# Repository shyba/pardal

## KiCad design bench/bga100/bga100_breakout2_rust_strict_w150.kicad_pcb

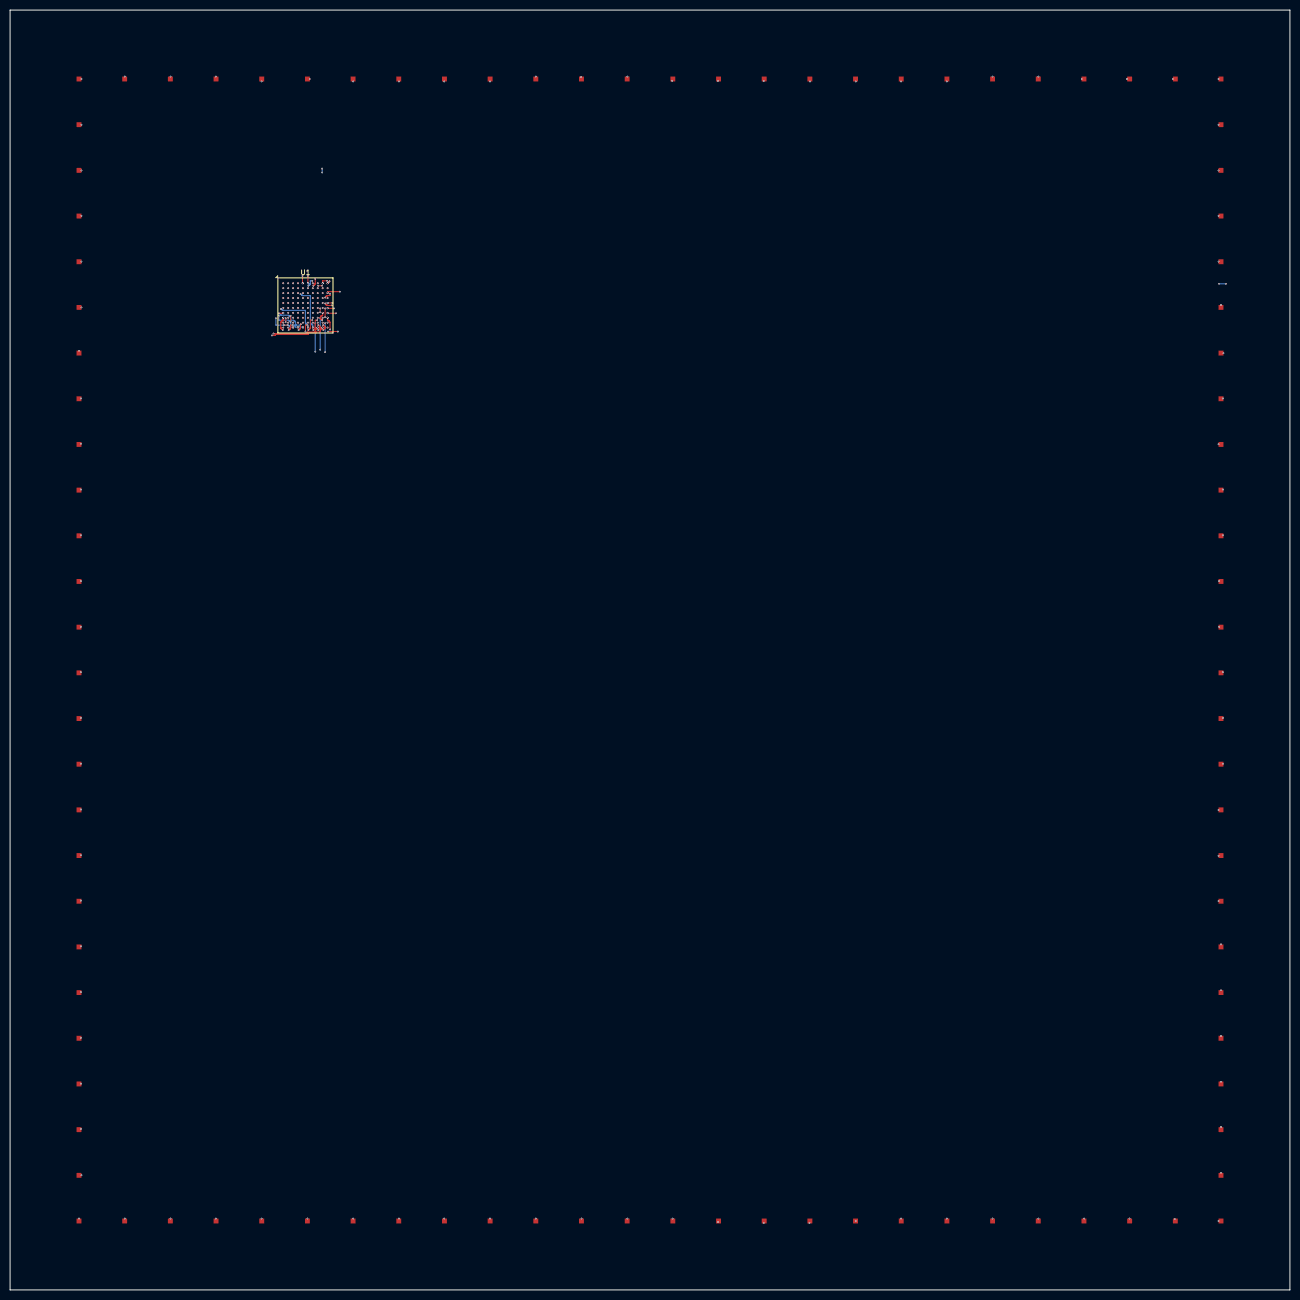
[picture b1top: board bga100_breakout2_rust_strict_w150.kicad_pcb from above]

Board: 4 copper layers, 260.0 x 260.0 mm, 101 parts (0 on the bottom side), 100 nets.

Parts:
TP1: A1; TestPoint_Pad_1.0x1.0mm
TP2: A2; TestPoint_Pad_1.0x1.0mm
TP3: A3; TestPoint_Pad_1.0x1.0mm
TP4: A4; TestPoint_Pad_1.0x1.0mm
TP5: A5; TestPoint_Pad_1.0x1.0mm
TP6: A6; TestPoint_Pad_1.0x1.0mm
TP7: A7; TestPoint_Pad_1.0x1.0mm
TP8: A8; TestPoint_Pad_1.0x1.0mm
TP9: A9; TestPoint_Pad_1.0x1.0mm
TP10: A10; TestPoint_Pad_1.0x1.0mm
TP11: B1; TestPoint_Pad_1.0x1.0mm
TP12: B2; TestPoint_Pad_1.0x1.0mm
TP13: B3; TestPoint_Pad_1.0x1.0mm
TP14: B4; TestPoint_Pad_1.0x1.0mm
TP15: B5; TestPoint_Pad_1.0x1.0mm
TP16: B6; TestPoint_Pad_1.0x1.0mm
TP17: B7; TestPoint_Pad_1.0x1.0mm
TP18: B8; TestPoint_Pad_1.0x1.0mm
TP19: B9; TestPoint_Pad_1.0x1.0mm
TP20: B10; TestPoint_Pad_1.0x1.0mm
TP21: C1; TestPoint_Pad_1.0x1.0mm
TP22: C2; TestPoint_Pad_1.0x1.0mm
TP23: C3; TestPoint_Pad_1.0x1.0mm
TP24: C4; TestPoint_Pad_1.0x1.0mm
TP25: C5; TestPoint_Pad_1.0x1.0mm
TP26: C6; TestPoint_Pad_1.0x1.0mm
TP27: C7; TestPoint_Pad_1.0x1.0mm
TP28: C8; TestPoint_Pad_1.0x1.0mm
TP29: C9; TestPoint_Pad_1.0x1.0mm
TP30: C10; TestPoint_Pad_1.0x1.0mm
TP31: D1; TestPoint_Pad_1.0x1.0mm
TP32: D2; TestPoint_Pad_1.0x1.0mm
TP33: D3; TestPoint_Pad_1.0x1.0mm
TP34: D4; TestPoint_Pad_1.0x1.0mm
TP35: D5; TestPoint_Pad_1.0x1.0mm
TP36: D6; TestPoint_Pad_1.0x1.0mm
TP37: D7; TestPoint_Pad_1.0x1.0mm
TP38: D8; TestPoint_Pad_1.0x1.0mm
TP39: D9; TestPoint_Pad_1.0x1.0mm
TP40: D10; TestPoint_Pad_1.0x1.0mm
TP41: E1; TestPoint_Pad_1.0x1.0mm
TP42: E2; TestPoint_Pad_1.0x1.0mm
TP43: E3; TestPoint_Pad_1.0x1.0mm
TP44: E4; TestPoint_Pad_1.0x1.0mm
TP45: E5; TestPoint_Pad_1.0x1.0mm
TP46: E6; TestPoint_Pad_1.0x1.0mm
TP47: E7; TestPoint_Pad_1.0x1.0mm
TP48: E8; TestPoint_Pad_1.0x1.0mm
TP49: E9; TestPoint_Pad_1.0x1.0mm
TP50: E10; TestPoint_Pad_1.0x1.0mm
TP51: F1; TestPoint_Pad_1.0x1.0mm
TP52: F2; TestPoint_Pad_1.0x1.0mm
TP53: F3; TestPoint_Pad_1.0x1.0mm
TP54: F4; TestPoint_Pad_1.0x1.0mm
TP55: F5; TestPoint_Pad_1.0x1.0mm
TP56: F6; TestPoint_Pad_1.0x1.0mm
TP57: F7; TestPoint_Pad_1.0x1.0mm
TP58: F8; TestPoint_Pad_1.0x1.0mm
TP59: F9; TestPoint_Pad_1.0x1.0mm
TP60: F10; TestPoint_Pad_1.0x1.0mm
TP61: G1; TestPoint_Pad_1.0x1.0mm
TP62: G2; TestPoint_Pad_1.0x1.0mm
TP63: G3; TestPoint_Pad_1.0x1.0mm
TP64: G4; TestPoint_Pad_1.0x1.0mm
TP65: G5; TestPoint_Pad_1.0x1.0mm
TP66: G6; TestPoint_Pad_1.0x1.0mm
TP67: G7; TestPoint_Pad_1.0x1.0mm
TP68: G8; TestPoint_Pad_1.0x1.0mm
TP69: G9; TestPoint_Pad_1.0x1.0mm
TP70: G10; TestPoint_Pad_1.0x1.0mm
TP71: H1; TestPoint_Pad_1.0x1.0mm
TP72: H2; TestPoint_Pad_1.0x1.0mm
TP73: H3; TestPoint_Pad_1.0x1.0mm
TP74: H4; TestPoint_Pad_1.0x1.0mm
TP75: H5; TestPoint_Pad_1.0x1.0mm
TP76: H6; TestPoint_Pad_1.0x1.0mm
TP77: H7; TestPoint_Pad_1.0x1.0mm
TP78: H8; TestPoint_Pad_1.0x1.0mm
TP79: H9; TestPoint_Pad_1.0x1.0mm
TP80: H10; TestPoint_Pad_1.0x1.0mm
TP81: J1; TestPoint_Pad_1.0x1.0mm
TP82: J2; TestPoint_Pad_1.0x1.0mm
TP83: J3; TestPoint_Pad_1.0x1.0mm
TP84: J4; TestPoint_Pad_1.0x1.0mm
TP85: J5; TestPoint_Pad_1.0x1.0mm
TP86: J6; TestPoint_Pad_1.0x1.0mm
TP87: J7; TestPoint_Pad_1.0x1.0mm
TP88: J8; TestPoint_Pad_1.0x1.0mm
TP89: J9; TestPoint_Pad_1.0x1.0mm
TP90: J10; TestPoint_Pad_1.0x1.0mm
TP91: K1; TestPoint_Pad_1.0x1.0mm
TP92: K2; TestPoint_Pad_1.0x1.0mm
TP93: K3; TestPoint_Pad_1.0x1.0mm
TP94: K4; TestPoint_Pad_1.0x1.0mm
TP95: K5; TestPoint_Pad_1.0x1.0mm
TP96: K6; TestPoint_Pad_1.0x1.0mm
TP97: K7; TestPoint_Pad_1.0x1.0mm
TP98: K8; TestPoint_Pad_1.0x1.0mm
TP99: K9; TestPoint_Pad_1.0x1.0mm
TP100: K10; TestPoint_Pad_1.0x1.0mm
U1: BGA-100_11.0x11.0mm_Layout10x10_P1.0mm_Ball0.5mm_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; BGA-100_11.0x11.0mm_Layout10x10_P1.0mm_Ball0.5mm_Pad0.4mm_N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

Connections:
U1_A1: TP1.1, U1.A1
U1_A2: TP2.1, U1.A2
U1_A3: TP3.1, U1.A3
U1_A4: TP4.1, U1.A4
U1_A5: TP5.1, U1.A5
U1_A6: TP6.1, U1.A6
U1_A7: TP7.1, U1.A7
U1_A8: TP8.1, U1.A8
U1_A9: TP9.1, U1.A9
U1_A10: TP10.1, U1.A10
U1_B1: TP11.1, U1.B1
U1_B2: TP12.1, U1.B2
U1_B3: TP13.1, U1.B3
U1_B4: TP14.1, U1.B4
U1_B5: TP15.1, U1.B5
U1_B6: TP16.1, U1.B6
U1_B7: TP17.1, U1.B7
U1_B8: TP18.1, U1.B8
U1_B9: TP19.1, U1.B9
U1_B10: TP20.1, U1.B10
U1_C1: TP21.1, U1.C1
U1_C2: TP22.1, U1.C2
U1_C3: TP23.1, U1.C3
U1_C4: TP24.1, U1.C4
U1_C5: TP25.1, U1.C5
U1_C6: TP26.1, U1.C6
U1_C7: TP27.1, U1.C7
U1_C8: TP28.1, U1.C8
U1_C9: TP29.1, U1.C9
U1_C10: TP30.1, U1.C10
U1_D1: TP31.1, U1.D1
U1_D2: TP32.1, U1.D2
U1_D3: TP33.1, U1.D3
U1_D4: TP34.1, U1.D4
U1_D5: TP35.1, U1.D5
U1_D6: TP36.1, U1.D6
U1_D7: TP37.1, U1.D7
U1_D8: TP38.1, U1.D8
U1_D9: TP39.1, U1.D9
U1_D10: TP40.1, U1.D10
U1_E1: TP41.1, U1.E1
U1_E2: TP42.1, U1.E2
U1_E3: TP43.1, U1.E3
U1_E4: TP44.1, U1.E4
U1_E5: TP45.1, U1.E5
U1_E6: TP46.1, U1.E6
U1_E7: TP47.1, U1.E7
U1_E8: TP48.1, U1.E8
U1_E9: TP49.1, U1.E9
U1_E10: TP50.1, U1.E10
U1_F1: TP51.1, U1.F1
U1_F2: TP52.1, U1.F2
U1_F3: TP53.1, U1.F3
U1_F4: TP54.1, U1.F4
U1_F5: TP55.1, U1.F5
U1_F6: TP56.1, U1.F6
U1_F7: TP57.1, U1.F7
U1_F8: TP58.1, U1.F8
U1_F9: TP59.1, U1.F9
U1_F10: TP60.1, U1.F10
U1_G1: TP61.1, U1.G1
U1_G2: TP62.1, U1.G2
U1_G3: TP63.1, U1.G3
U1_G4: TP64.1, U1.G4
U1_G5: TP65.1, U1.G5
U1_G6: TP66.1, U1.G6
U1_G7: TP67.1, U1.G7
U1_G8: TP68.1, U1.G8
U1_G9: TP69.1, U1.G9
U1_G10: TP70.1, U1.G10
U1_H1: TP71.1, U1.H1
U1_H2: TP72.1, U1.H2
U1_H3: TP73.1, U1.H3
U1_H4: TP74.1, U1.H4
U1_H5: TP75.1, U1.H5
U1_H6: TP76.1, U1.H6
U1_H7: TP77.1, U1.H7
U1_H8: TP78.1, U1.H8
U1_H9: TP79.1, U1.H9
U1_H10: TP80.1, U1.H10
U1_J1: TP81.1, U1.J1
U1_J2: TP82.1, U1.J2
U1_J3: TP83.1, U1.J3
U1_J4: TP84.1, U1.J4
U1_J5: TP85.1, U1.J5
U1_J6: TP86.1, U1.J6
U1_J7: TP87.1, U1.J7
U1_J8: TP88.1, U1.J8
U1_J9: TP89.1, U1.J9
U1_J10: TP90.1, U1.J10
U1_K1: TP91.1, U1.K1
U1_K2: TP92.1, U1.K2
U1_K3: TP93.1, U1.K3
U1_K4: TP94.1, U1.K4
U1_K5: TP95.1, U1.K5
U1_K6: TP96.1, U1.K6
U1_K7: TP97.1, U1.K7
U1_K8: TP98.1, U1.K8
U1_K9: TP99.1, U1.K9
U1_K10: TP100.1, U1.K10

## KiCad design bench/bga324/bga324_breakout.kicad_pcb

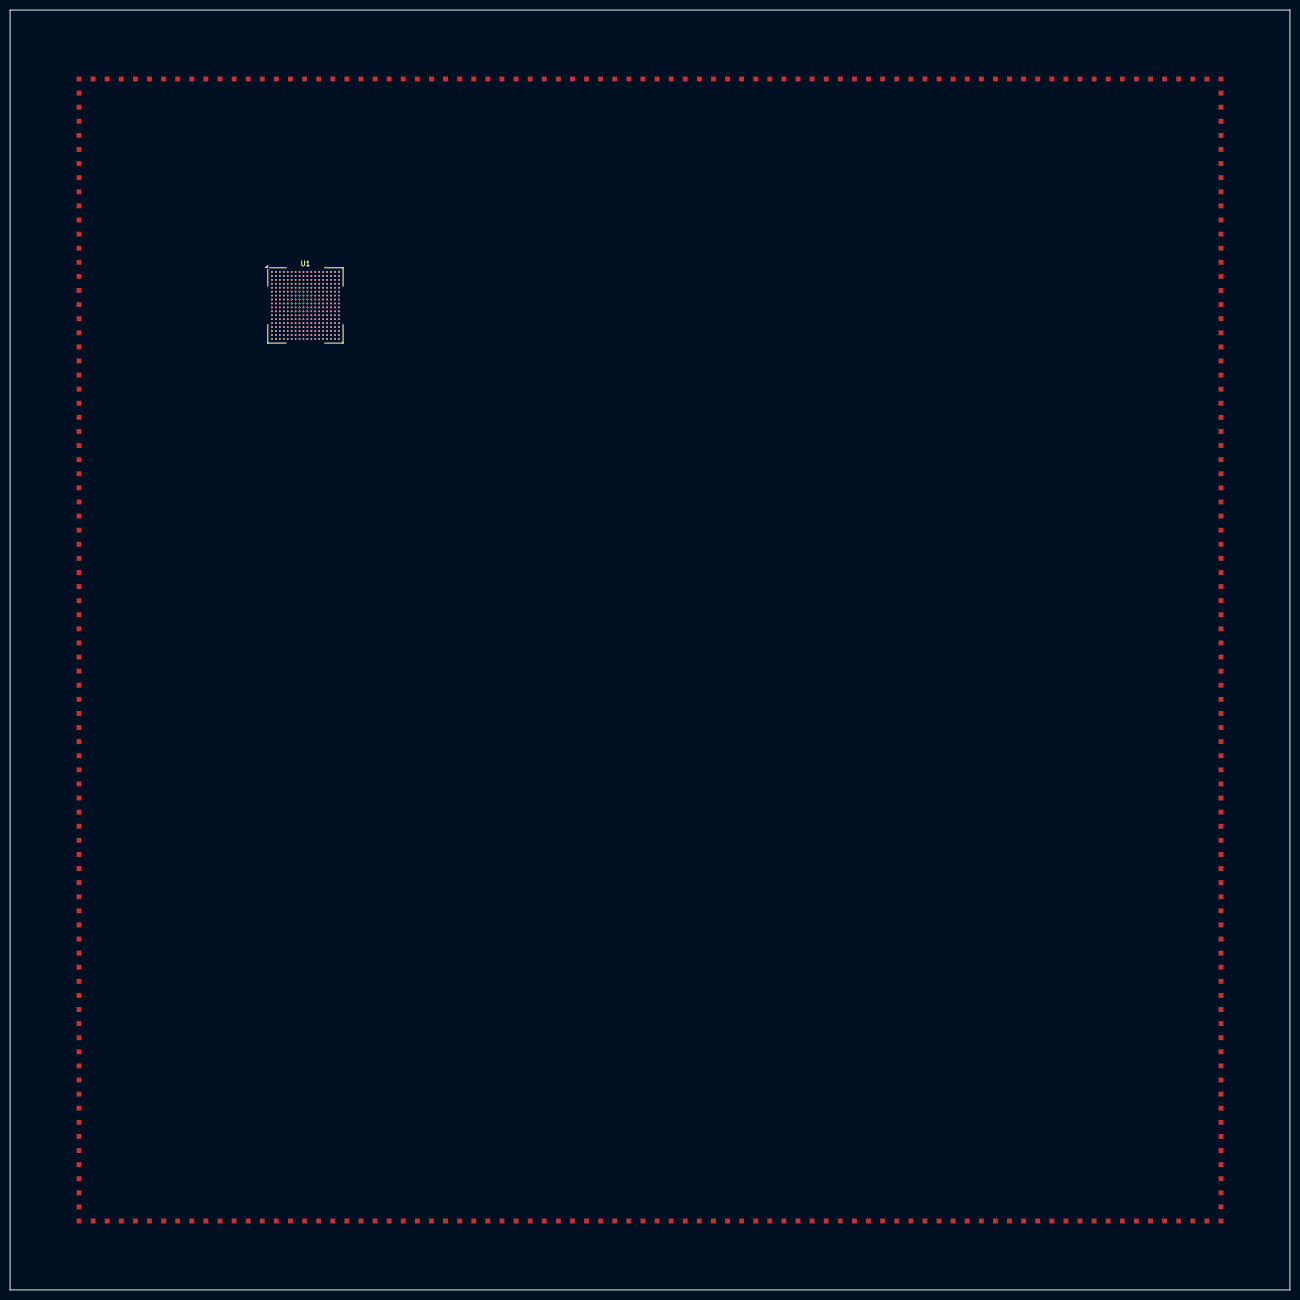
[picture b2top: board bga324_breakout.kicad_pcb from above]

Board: 4 copper layers, 260.0 x 260.0 mm, 325 parts (0 on the bottom side), 324 nets.

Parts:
TP1: A1; TestPoint_Pad_1.0x1.0mm
TP2: A2; TestPoint_Pad_1.0x1.0mm
TP3: A3; TestPoint_Pad_1.0x1.0mm
TP4: A4; TestPoint_Pad_1.0x1.0mm
TP5: A5; TestPoint_Pad_1.0x1.0mm
TP6: A6; TestPoint_Pad_1.0x1.0mm
TP7: A7; TestPoint_Pad_1.0x1.0mm
TP8: A8; TestPoint_Pad_1.0x1.0mm
TP9: A9; TestPoint_Pad_1.0x1.0mm
TP10: A10; TestPoint_Pad_1.0x1.0mm
TP11: A11; TestPoint_Pad_1.0x1.0mm
TP12: A12; TestPoint_Pad_1.0x1.0mm
TP13: A13; TestPoint_Pad_1.0x1.0mm
TP14: A14; TestPoint_Pad_1.0x1.0mm
TP15: A15; TestPoint_Pad_1.0x1.0mm
TP16: A16; TestPoint_Pad_1.0x1.0mm
TP17: A17; TestPoint_Pad_1.0x1.0mm
TP18: A18; TestPoint_Pad_1.0x1.0mm
TP19: B1; TestPoint_Pad_1.0x1.0mm
TP20: B2; TestPoint_Pad_1.0x1.0mm
TP21: B3; TestPoint_Pad_1.0x1.0mm
TP22: B4; TestPoint_Pad_1.0x1.0mm
TP23: B5; TestPoint_Pad_1.0x1.0mm
TP24: B6; TestPoint_Pad_1.0x1.0mm
TP25: B7; TestPoint_Pad_1.0x1.0mm
TP26: B8; TestPoint_Pad_1.0x1.0mm
TP27: B9; TestPoint_Pad_1.0x1.0mm
TP28: B10; TestPoint_Pad_1.0x1.0mm
TP29: B11; TestPoint_Pad_1.0x1.0mm
TP30: B12; TestPoint_Pad_1.0x1.0mm
TP31: B13; TestPoint_Pad_1.0x1.0mm
TP32: B14; TestPoint_Pad_1.0x1.0mm
TP33: B15; TestPoint_Pad_1.0x1.0mm
TP34: B16; TestPoint_Pad_1.0x1.0mm
TP35: B17; TestPoint_Pad_1.0x1.0mm
TP36: B18; TestPoint_Pad_1.0x1.0mm
TP37: C1; TestPoint_Pad_1.0x1.0mm
TP38: C2; TestPoint_Pad_1.0x1.0mm
TP39: C3; TestPoint_Pad_1.0x1.0mm
TP40: C4; TestPoint_Pad_1.0x1.0mm
TP41: C5; TestPoint_Pad_1.0x1.0mm
TP42: C6; TestPoint_Pad_1.0x1.0mm
TP43: C7; TestPoint_Pad_1.0x1.0mm
TP44: C8; TestPoint_Pad_1.0x1.0mm
TP45: C9; TestPoint_Pad_1.0x1.0mm
TP46: C10; TestPoint_Pad_1.0x1.0mm
TP47: C11; TestPoint_Pad_1.0x1.0mm
TP48: C12; TestPoint_Pad_1.0x1.0mm
TP49: C13; TestPoint_Pad_1.0x1.0mm
TP50: C14; TestPoint_Pad_1.0x1.0mm
TP51: C15; TestPoint_Pad_1.0x1.0mm
TP52: C16; TestPoint_Pad_1.0x1.0mm
TP53: C17; TestPoint_Pad_1.0x1.0mm
TP54: C18; TestPoint_Pad_1.0x1.0mm
TP55: D1; TestPoint_Pad_1.0x1.0mm
TP56: D2; TestPoint_Pad_1.0x1.0mm
TP57: D3; TestPoint_Pad_1.0x1.0mm
TP58: D4; TestPoint_Pad_1.0x1.0mm
TP59: D5; TestPoint_Pad_1.0x1.0mm
TP60: D6; TestPoint_Pad_1.0x1.0mm
TP61: D7; TestPoint_Pad_1.0x1.0mm
TP62: D8; TestPoint_Pad_1.0x1.0mm
TP63: D9; TestPoint_Pad_1.0x1.0mm
TP64: D10; TestPoint_Pad_1.0x1.0mm
TP65: D11; TestPoint_Pad_1.0x1.0mm
TP66: D12; TestPoint_Pad_1.0x1.0mm
TP67: D13; TestPoint_Pad_1.0x1.0mm
TP68: D14; TestPoint_Pad_1.0x1.0mm
TP69: D15; TestPoint_Pad_1.0x1.0mm
TP70: D16; TestPoint_Pad_1.0x1.0mm
TP71: D17; TestPoint_Pad_1.0x1.0mm
TP72: D18; TestPoint_Pad_1.0x1.0mm
TP73: E1; TestPoint_Pad_1.0x1.0mm
TP74: E2; TestPoint_Pad_1.0x1.0mm
TP75: E3; TestPoint_Pad_1.0x1.0mm
TP76: E4; TestPoint_Pad_1.0x1.0mm
TP77: E5; TestPoint_Pad_1.0x1.0mm
TP78: E6; TestPoint_Pad_1.0x1.0mm
TP79: E7; TestPoint_Pad_1.0x1.0mm
TP80: E8; TestPoint_Pad_1.0x1.0mm
TP81: E9; TestPoint_Pad_1.0x1.0mm
TP82: E10; TestPoint_Pad_1.0x1.0mm
TP83: E11; TestPoint_Pad_1.0x1.0mm
TP84: E12; TestPoint_Pad_1.0x1.0mm
TP85: E13; TestPoint_Pad_1.0x1.0mm
TP86: E14; TestPoint_Pad_1.0x1.0mm
TP87: E15; TestPoint_Pad_1.0x1.0mm
TP88: E16; TestPoint_Pad_1.0x1.0mm
TP89: E17; TestPoint_Pad_1.0x1.0mm
TP90: E18; TestPoint_Pad_1.0x1.0mm
TP91: F1; TestPoint_Pad_1.0x1.0mm
TP92: F2; TestPoint_Pad_1.0x1.0mm
TP93: F3; TestPoint_Pad_1.0x1.0mm
TP94: F4; TestPoint_Pad_1.0x1.0mm
TP95: F5; TestPoint_Pad_1.0x1.0mm
TP96: F6; TestPoint_Pad_1.0x1.0mm
TP97: F7; TestPoint_Pad_1.0x1.0mm
TP98: F8; TestPoint_Pad_1.0x1.0mm
TP99: F9; TestPoint_Pad_1.0x1.0mm
TP100: F10; TestPoint_Pad_1.0x1.0mm
TP101: F11; TestPoint_Pad_1.0x1.0mm
TP102: F12; TestPoint_Pad_1.0x1.0mm
TP103: F13; TestPoint_Pad_1.0x1.0mm
TP104: F14; TestPoint_Pad_1.0x1.0mm
TP105: F15; TestPoint_Pad_1.0x1.0mm
TP106: F16; TestPoint_Pad_1.0x1.0mm
TP107: F17; TestPoint_Pad_1.0x1.0mm
TP108: F18; TestPoint_Pad_1.0x1.0mm
TP109: G1; TestPoint_Pad_1.0x1.0mm
TP110: G2; TestPoint_Pad_1.0x1.0mm
TP111: G3; TestPoint_Pad_1.0x1.0mm
TP112: G4; TestPoint_Pad_1.0x1.0mm
TP113: G5; TestPoint_Pad_1.0x1.0mm
TP114: G6; TestPoint_Pad_1.0x1.0mm
TP115: G7; TestPoint_Pad_1.0x1.0mm
TP116: G8; TestPoint_Pad_1.0x1.0mm
TP117: G9; TestPoint_Pad_1.0x1.0mm
TP118: G10; TestPoint_Pad_1.0x1.0mm
TP119: G11; TestPoint_Pad_1.0x1.0mm
TP120: G12; TestPoint_Pad_1.0x1.0mm
TP121: G13; TestPoint_Pad_1.0x1.0mm
TP122: G14; TestPoint_Pad_1.0x1.0mm
TP123: G15; TestPoint_Pad_1.0x1.0mm
TP124: G16; TestPoint_Pad_1.0x1.0mm
TP125: G17; TestPoint_Pad_1.0x1.0mm
TP126: G18; TestPoint_Pad_1.0x1.0mm
TP127: H1; TestPoint_Pad_1.0x1.0mm
TP128: H2; TestPoint_Pad_1.0x1.0mm
TP129: H3; TestPoint_Pad_1.0x1.0mm
TP130: H4; TestPoint_Pad_1.0x1.0mm
TP131: H5; TestPoint_Pad_1.0x1.0mm
TP132: H6; TestPoint_Pad_1.0x1.0mm
TP133: H7; TestPoint_Pad_1.0x1.0mm
TP134: H8; TestPoint_Pad_1.0x1.0mm
TP135: H9; TestPoint_Pad_1.0x1.0mm
TP136: H10; TestPoint_Pad_1.0x1.0mm
TP137: H11; TestPoint_Pad_1.0x1.0mm
TP138: H12; TestPoint_Pad_1.0x1.0mm
TP139: H13; TestPoint_Pad_1.0x1.0mm
TP140: H14; TestPoint_Pad_1.0x1.0mm
TP141: H15; TestPoint_Pad_1.0x1.0mm
TP142: H16; TestPoint_Pad_1.0x1.0mm
TP143: H17; TestPoint_Pad_1.0x1.0mm
TP144: H18; TestPoint_Pad_1.0x1.0mm
TP145: J1; TestPoint_Pad_1.0x1.0mm
TP146: J2; TestPoint_Pad_1.0x1.0mm
TP147: J3; TestPoint_Pad_1.0x1.0mm
TP148: J4; TestPoint_Pad_1.0x1.0mm
TP149: J5; TestPoint_Pad_1.0x1.0mm
TP150: J6; TestPoint_Pad_1.0x1.0mm
TP151: J7; TestPoint_Pad_1.0x1.0mm
TP152: J8; TestPoint_Pad_1.0x1.0mm
TP153: J9; TestPoint_Pad_1.0x1.0mm
TP154: J10; TestPoint_Pad_1.0x1.0mm
TP155: J11; TestPoint_Pad_1.0x1.0mm
TP156: J12; TestPoint_Pad_1.0x1.0mm
TP157: J13; TestPoint_Pad_1.0x1.0mm
TP158: J14; TestPoint_Pad_1.0x1.0mm
TP159: J15; TestPoint_Pad_1.0x1.0mm
TP160: J16; TestPoint_Pad_1.0x1.0mm
TP161: J17; TestPoint_Pad_1.0x1.0mm
TP162: J18; TestPoint_Pad_1.0x1.0mm
TP163: K1; TestPoint_Pad_1.0x1.0mm
TP164: K2; TestPoint_Pad_1.0x1.0mm
TP165: K3; TestPoint_Pad_1.0x1.0mm
TP166: K4; TestPoint_Pad_1.0x1.0mm
TP167: K5; TestPoint_Pad_1.0x1.0mm
TP168: K6; TestPoint_Pad_1.0x1.0mm
TP169: K7; TestPoint_Pad_1.0x1.0mm
TP170: K8; TestPoint_Pad_1.0x1.0mm
TP171: K9; TestPoint_Pad_1.0x1.0mm
TP172: K10; TestPoint_Pad_1.0x1.0mm
TP173: K11; TestPoint_Pad_1.0x1.0mm
TP174: K12; TestPoint_Pad_1.0x1.0mm
TP175: K13; TestPoint_Pad_1.0x1.0mm
TP176: K14; TestPoint_Pad_1.0x1.0mm
TP177: K15; TestPoint_Pad_1.0x1.0mm
TP178: K16; TestPoint_Pad_1.0x1.0mm
TP179: K17; TestPoint_Pad_1.0x1.0mm
TP180: K18; TestPoint_Pad_1.0x1.0mm
TP181: L1; TestPoint_Pad_1.0x1.0mm
TP182: L2; TestPoint_Pad_1.0x1.0mm
TP183: L3; TestPoint_Pad_1.0x1.0mm
TP184: L4; TestPoint_Pad_1.0x1.0mm
TP185: L5; TestPoint_Pad_1.0x1.0mm
TP186: L6; TestPoint_Pad_1.0x1.0mm
TP187: L7; TestPoint_Pad_1.0x1.0mm
TP188: L8; TestPoint_Pad_1.0x1.0mm
TP189: L9; TestPoint_Pad_1.0x1.0mm
TP190: L10; TestPoint_Pad_1.0x1.0mm
TP191: L11; TestPoint_Pad_1.0x1.0mm
TP192: L12; TestPoint_Pad_1.0x1.0mm
TP193: L13; TestPoint_Pad_1.0x1.0mm
TP194: L14; TestPoint_Pad_1.0x1.0mm
TP195: L15; TestPoint_Pad_1.0x1.0mm
TP196: L16; TestPoint_Pad_1.0x1.0mm
TP197: L17; TestPoint_Pad_1.0x1.0mm
TP198: L18; TestPoint_Pad_1.0x1.0mm
TP199: M1; TestPoint_Pad_1.0x1.0mm
TP200: M2; TestPoint_Pad_1.0x1.0mm
TP201: M3; TestPoint_Pad_1.0x1.0mm
TP202: M4; TestPoint_Pad_1.0x1.0mm
TP203: M5; TestPoint_Pad_1.0x1.0mm
TP204: M6; TestPoint_Pad_1.0x1.0mm
TP205: M7; TestPoint_Pad_1.0x1.0mm
TP206: M8; TestPoint_Pad_1.0x1.0mm
TP207: M9; TestPoint_Pad_1.0x1.0mm
TP208: M10; TestPoint_Pad_1.0x1.0mm
TP209: M11; TestPoint_Pad_1.0x1.0mm
TP210: M12; TestPoint_Pad_1.0x1.0mm
TP211: M13; TestPoint_Pad_1.0x1.0mm
TP212: M14; TestPoint_Pad_1.0x1.0mm
TP213: M15; TestPoint_Pad_1.0x1.0mm
TP214: M16; TestPoint_Pad_1.0x1.0mm
TP215: M17; TestPoint_Pad_1.0x1.0mm
TP216: M18; TestPoint_Pad_1.0x1.0mm
TP217: N1; TestPoint_Pad_1.0x1.0mm
TP218: N2; TestPoint_Pad_1.0x1.0mm
TP219: N3; TestPoint_Pad_1.0x1.0mm
TP220: N4; TestPoint_Pad_1.0x1.0mm
TP221: N5; TestPoint_Pad_1.0x1.0mm
TP222: N6; TestPoint_Pad_1.0x1.0mm
TP223: N7; TestPoint_Pad_1.0x1.0mm
TP224: N8; TestPoint_Pad_1.0x1.0mm
TP225: N9; TestPoint_Pad_1.0x1.0mm
TP226: N10; TestPoint_Pad_1.0x1.0mm
TP227: N11; TestPoint_Pad_1.0x1.0mm
TP228: N12; TestPoint_Pad_1.0x1.0mm
TP229: N13; TestPoint_Pad_1.0x1.0mm
TP230: N14; TestPoint_Pad_1.0x1.0mm
TP231: N15; TestPoint_Pad_1.0x1.0mm
TP232: N16; TestPoint_Pad_1.0x1.0mm
TP233: N17; TestPoint_Pad_1.0x1.0mm
TP234: N18; TestPoint_Pad_1.0x1.0mm
TP235: P1; TestPoint_Pad_1.0x1.0mm
TP236: P2; TestPoint_Pad_1.0x1.0mm
TP237: P3; TestPoint_Pad_1.0x1.0mm
TP238: P4; TestPoint_Pad_1.0x1.0mm
TP239: P5; TestPoint_Pad_1.0x1.0mm
TP240: P6; TestPoint_Pad_1.0x1.0mm
TP241: P7; TestPoint_Pad_1.0x1.0mm
TP242: P8; TestPoint_Pad_1.0x1.0mm
TP243: P9; TestPoint_Pad_1.0x1.0mm
TP244: P10; TestPoint_Pad_1.0x1.0mm
TP245: P11; TestPoint_Pad_1.0x1.0mm
TP246: P12; TestPoint_Pad_1.0x1.0mm
TP247: P13; TestPoint_Pad_1.0x1.0mm
TP248: P14; TestPoint_Pad_1.0x1.0mm
TP249: P15; TestPoint_Pad_1.0x1.0mm
TP250: P16; TestPoint_Pad_1.0x1.0mm
TP251: P17; TestPoint_Pad_1.0x1.0mm
TP252: P18; TestPoint_Pad_1.0x1.0mm
TP253: R1; TestPoint_Pad_1.0x1.0mm
TP254: R2; TestPoint_Pad_1.0x1.0mm
TP255: R3; TestPoint_Pad_1.0x1.0mm
TP256: R4; TestPoint_Pad_1.0x1.0mm
TP257: R5; TestPoint_Pad_1.0x1.0mm
TP258: R6; TestPoint_Pad_1.0x1.0mm
TP259: R7; TestPoint_Pad_1.0x1.0mm
TP260: R8; TestPoint_Pad_1.0x1.0mm
TP261: R9; TestPoint_Pad_1.0x1.0mm
TP262: R10; TestPoint_Pad_1.0x1.0mm
TP263: R11; TestPoint_Pad_1.0x1.0mm
TP264: R12; TestPoint_Pad_1.0x1.0mm
TP265: R13; TestPoint_Pad_1.0x1.0mm
TP266: R14; TestPoint_Pad_1.0x1.0mm
TP267: R15; TestPoint_Pad_1.0x1.0mm
TP268: R16; TestPoint_Pad_1.0x1.0mm
TP269: R17; TestPoint_Pad_1.0x1.0mm
TP270: R18; TestPoint_Pad_1.0x1.0mm
TP271: T1; TestPoint_Pad_1.0x1.0mm
TP272: T2; TestPoint_Pad_1.0x1.0mm
TP273: T3; TestPoint_Pad_1.0x1.0mm
TP274: T4; TestPoint_Pad_1.0x1.0mm
TP275: T5; TestPoint_Pad_1.0x1.0mm
TP276: T6; TestPoint_Pad_1.0x1.0mm
TP277: T7; TestPoint_Pad_1.0x1.0mm
TP278: T8; TestPoint_Pad_1.0x1.0mm
TP279: T9; TestPoint_Pad_1.0x1.0mm
TP280: T10; TestPoint_Pad_1.0x1.0mm
TP281: T11; TestPoint_Pad_1.0x1.0mm
TP282: T12; TestPoint_Pad_1.0x1.0mm
TP283: T13; TestPoint_Pad_1.0x1.0mm
TP284: T14; TestPoint_Pad_1.0x1.0mm
TP285: T15; TestPoint_Pad_1.0x1.0mm
TP286: T16; TestPoint_Pad_1.0x1.0mm
TP287: T17; TestPoint_Pad_1.0x1.0mm
TP288: T18; TestPoint_Pad_1.0x1.0mm
TP289: U1; TestPoint_Pad_1.0x1.0mm
TP290: U2; TestPoint_Pad_1.0x1.0mm
TP291: U3; TestPoint_Pad_1.0x1.0mm
TP292: U4; TestPoint_Pad_1.0x1.0mm
TP293: U5; TestPoint_Pad_1.0x1.0mm
TP294: U6; TestPoint_Pad_1.0x1.0mm
TP295: U7; TestPoint_Pad_1.0x1.0mm
TP296: U8; TestPoint_Pad_1.0x1.0mm
TP297: U9; TestPoint_Pad_1.0x1.0mm
TP298: U10; TestPoint_Pad_1.0x1.0mm
TP299: U11; TestPoint_Pad_1.0x1.0mm
TP300: U12; TestPoint_Pad_1.0x1.0mm
TP301: U13; TestPoint_Pad_1.0x1.0mm
TP302: U14; TestPoint_Pad_1.0x1.0mm
TP303: U15; TestPoint_Pad_1.0x1.0mm
TP304: U16; TestPoint_Pad_1.0x1.0mm
TP305: U17; TestPoint_Pad_1.0x1.0mm
TP306: U18; TestPoint_Pad_1.0x1.0mm
TP307: V1; TestPoint_Pad_1.0x1.0mm
TP308: V2; TestPoint_Pad_1.0x1.0mm
TP309: V3; TestPoint_Pad_1.0x1.0mm
TP310: V4; TestPoint_Pad_1.0x1.0mm
TP311: V5; TestPoint_Pad_1.0x1.0mm
TP312: V6; TestPoint_Pad_1.0x1.0mm
TP313: V7; TestPoint_Pad_1.0x1.0mm
TP314: V8; TestPoint_Pad_1.0x1.0mm
TP315: V9; TestPoint_Pad_1.0x1.0mm
TP316: V10; TestPoint_Pad_1.0x1.0mm
TP317: V11; TestPoint_Pad_1.0x1.0mm
TP318: V12; TestPoint_Pad_1.0x1.0mm
TP319: V13; TestPoint_Pad_1.0x1.0mm
TP320: V14; TestPoint_Pad_1.0x1.0mm
TP321: V15; TestPoint_Pad_1.0x1.0mm
TP322: V16; TestPoint_Pad_1.0x1.0mm
TP323: V17; TestPoint_Pad_1.0x1.0mm
TP324: V18; TestPoint_Pad_1.0x1.0mm
U1: BGA-324_15.0x15.0mm_Layout18x18_P0.8mm_Ball0.5mm_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; BGA-324_15.0x15.0mm_Layout18x18_P0.8mm_Ball0.5mm_Pad0.4mm_N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

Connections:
U1_A1: TP1.1, U1.A1
U1_A2: TP2.1, U1.A2
U1_A3: TP3.1, U1.A3
U1_A4: TP4.1, U1.A4
U1_A5: TP5.1, U1.A5
U1_A6: TP6.1, U1.A6
U1_A7: TP7.1, U1.A7
U1_A8: TP8.1, U1.A8
U1_A9: TP9.1, U1.A9
U1_A10: TP10.1, U1.A10
U1_A11: TP11.1, U1.A11
U1_A12: TP12.1, U1.A12
U1_A13: TP13.1, U1.A13
U1_A14: TP14.1, U1.A14
U1_A15: TP15.1, U1.A15
U1_A16: TP16.1, U1.A16
U1_A17: TP17.1, U1.A17
U1_A18: TP18.1, U1.A18
U1_B1: TP19.1, U1.B1
U1_B2: TP20.1, U1.B2
U1_B3: TP21.1, U1.B3
U1_B4: TP22.1, U1.B4
U1_B5: TP23.1, U1.B5
U1_B6: TP24.1, U1.B6
U1_B7: TP25.1, U1.B7
U1_B8: TP26.1, U1.B8
U1_B9: TP27.1, U1.B9
U1_B10: TP28.1, U1.B10
U1_B11: TP29.1, U1.B11
U1_B12: TP30.1, U1.B12
U1_B13: TP31.1, U1.B13
U1_B14: TP32.1, U1.B14
U1_B15: TP33.1, U1.B15
U1_B16: TP34.1, U1.B16
U1_B17: TP35.1, U1.B17
U1_B18: TP36.1, U1.B18
U1_C1: TP37.1, U1.C1
U1_C2: TP38.1, U1.C2
U1_C3: TP39.1, U1.C3
U1_C4: TP40.1, U1.C4
U1_C5: TP41.1, U1.C5
U1_C6: TP42.1, U1.C6
U1_C7: TP43.1, U1.C7
U1_C8: TP44.1, U1.C8
U1_C9: TP45.1, U1.C9
U1_C10: TP46.1, U1.C10
U1_C11: TP47.1, U1.C11
U1_C12: TP48.1, U1.C12
U1_C13: TP49.1, U1.C13
U1_C14: TP50.1, U1.C14
U1_C15: TP51.1, U1.C15
U1_C16: TP52.1, U1.C16
U1_C17: TP53.1, U1.C17
U1_C18: TP54.1, U1.C18
U1_D1: TP55.1, U1.D1
U1_D2: TP56.1, U1.D2
U1_D3: TP57.1, U1.D3
U1_D4: TP58.1, U1.D4
U1_D5: TP59.1, U1.D5
U1_D6: TP60.1, U1.D6
U1_D7: TP61.1, U1.D7
U1_D8: TP62.1, U1.D8
U1_D9: TP63.1, U1.D9
U1_D10: TP64.1, U1.D10
U1_D11: TP65.1, U1.D11
U1_D12: TP66.1, U1.D12
U1_D13: TP67.1, U1.D13
U1_D14: TP68.1, U1.D14
U1_D15: TP69.1, U1.D15
U1_D16: TP70.1, U1.D16
U1_D17: TP71.1, U1.D17
U1_D18: TP72.1, U1.D18
U1_E1: TP73.1, U1.E1
U1_E2: TP74.1, U1.E2
U1_E3: TP75.1, U1.E3
U1_E4: TP76.1, U1.E4
U1_E5: TP77.1, U1.E5
U1_E6: TP78.1, U1.E6
U1_E7: TP79.1, U1.E7
U1_E8: TP80.1, U1.E8
U1_E9: TP81.1, U1.E9
U1_E10: TP82.1, U1.E10
U1_E11: TP83.1, U1.E11
U1_E12: TP84.1, U1.E12
U1_E13: TP85.1, U1.E13
U1_E14: TP86.1, U1.E14
U1_E15: TP87.1, U1.E15
U1_E16: TP88.1, U1.E16
U1_E17: TP89.1, U1.E17
U1_E18: TP90.1, U1.E18
U1_F1: TP91.1, U1.F1
U1_F2: TP92.1, U1.F2
U1_F3: TP93.1, U1.F3
U1_F4: TP94.1, U1.F4
U1_F5: TP95.1, U1.F5
U1_F6: TP96.1, U1.F6
U1_F7: TP97.1, U1.F7
U1_F8: TP98.1, U1.F8
U1_F9: TP99.1, U1.F9
U1_F10: TP100.1, U1.F10
U1_F11: TP101.1, U1.F11
U1_F12: TP102.1, U1.F12
U1_F13: TP103.1, U1.F13
U1_F14: TP104.1, U1.F14
U1_F15: TP105.1, U1.F15
U1_F16: TP106.1, U1.F16
U1_F17: TP107.1, U1.F17
U1_F18: TP108.1, U1.F18
U1_G1: TP109.1, U1.G1
U1_G2: TP110.1, U1.G2
U1_G3: TP111.1, U1.G3
U1_G4: TP112.1, U1.G4
U1_G5: TP113.1, U1.G5
U1_G6: TP114.1, U1.G6
U1_G7: TP115.1, U1.G7
U1_G8: TP116.1, U1.G8
U1_G9: TP117.1, U1.G9
U1_G10: TP118.1, U1.G10
U1_G11: TP119.1, U1.G11
U1_G12: TP120.1, U1.G12
U1_G13: TP121.1, U1.G13
U1_G14: TP122.1, U1.G14
U1_G15: TP123.1, U1.G15
U1_G16: TP124.1, U1.G16
U1_G17: TP125.1, U1.G17
U1_G18: TP126.1, U1.G18
U1_H1: TP127.1, U1.H1
U1_H2: TP128.1, U1.H2
U1_H3: TP129.1, U1.H3
U1_H4: TP130.1, U1.H4
U1_H5: TP131.1, U1.H5
U1_H6: TP132.1, U1.H6
U1_H7: TP133.1, U1.H7
U1_H8: TP134.1, U1.H8
U1_H9: TP135.1, U1.H9
U1_H10: TP136.1, U1.H10
U1_H11: TP137.1, U1.H11
U1_H12: TP138.1, U1.H12
U1_H13: TP139.1, U1.H13
U1_H14: TP140.1, U1.H14
U1_H15: TP141.1, U1.H15
U1_H16: TP142.1, U1.H16
U1_H17: TP143.1, U1.H17
U1_H18: TP144.1, U1.H18
U1_J1: TP145.1, U1.J1
U1_J2: TP146.1, U1.J2
U1_J3: TP147.1, U1.J3
U1_J4: TP148.1, U1.J4
U1_J5: TP149.1, U1.J5
U1_J6: TP150.1, U1.J6
U1_J7: TP151.1, U1.J7
U1_J8: TP152.1, U1.J8
U1_J9: TP153.1, U1.J9
U1_J10: TP154.1, U1.J10
U1_J11: TP155.1, U1.J11
U1_J12: TP156.1, U1.J12
U1_J13: TP157.1, U1.J13
U1_J14: TP158.1, U1.J14
U1_J15: TP159.1, U1.J15
U1_J16: TP160.1, U1.J16
U1_J17: TP161.1, U1.J17
U1_J18: TP162.1, U1.J18
U1_K1: TP163.1, U1.K1
U1_K2: TP164.1, U1.K2
U1_K3: TP165.1, U1.K3
U1_K4: TP166.1, U1.K4
U1_K5: TP167.1, U1.K5
U1_K6: TP168.1, U1.K6
U1_K7: TP169.1, U1.K7
U1_K8: TP170.1, U1.K8
U1_K9: TP171.1, U1.K9
U1_K10: TP172.1, U1.K10
U1_K11: TP173.1, U1.K11
U1_K12: TP174.1, U1.K12
U1_K13: TP175.1, U1.K13
U1_K14: TP176.1, U1.K14
U1_K15: TP177.1, U1.K15
U1_K16: TP178.1, U1.K16
U1_K17: TP179.1, U1.K17
U1_K18: TP180.1, U1.K18
U1_L1: TP181.1, U1.L1
U1_L2: TP182.1, U1.L2
U1_L3: TP183.1, U1.L3
U1_L4: TP184.1, U1.L4
U1_L5: TP185.1, U1.L5
U1_L6: TP186.1, U1.L6
U1_L7: TP187.1, U1.L7
U1_L8: TP188.1, U1.L8
U1_L9: TP189.1, U1.L9
U1_L10: TP190.1, U1.L10
U1_L11: TP191.1, U1.L11
U1_L12: TP192.1, U1.L12
U1_L13: TP193.1, U1.L13
U1_L14: TP194.1, U1.L14
U1_L15: TP195.1, U1.L15
U1_L16: TP196.1, U1.L16
U1_L17: TP197.1, U1.L17
U1_L18: TP198.1, U1.L18
U1_M1: TP199.1, U1.M1
U1_M2: TP200.1, U1.M2
U1_M3: TP201.1, U1.M3
U1_M4: TP202.1, U1.M4
U1_M5: TP203.1, U1.M5
U1_M6: TP204.1, U1.M6
U1_M7: TP205.1, U1.M7
U1_M8: TP206.1, U1.M8
U1_M9: TP207.1, U1.M9
U1_M10: TP208.1, U1.M10
U1_M11: TP209.1, U1.M11
U1_M12: TP210.1, U1.M12
U1_M13: TP211.1, U1.M13
U1_M14: TP212.1, U1.M14
U1_M15: TP213.1, U1.M15
U1_M16: TP214.1, U1.M16
U1_M17: TP215.1, U1.M17
U1_M18: TP216.1, U1.M18
U1_N1: TP217.1, U1.N1
U1_N2: TP218.1, U1.N2
U1_N3: TP219.1, U1.N3
U1_N4: TP220.1, U1.N4
U1_N5: TP221.1, U1.N5
U1_N6: TP222.1, U1.N6
U1_N7: TP223.1, U1.N7
U1_N8: TP224.1, U1.N8
U1_N9: TP225.1, U1.N9
U1_N10: TP226.1, U1.N10
U1_N11: TP227.1, U1.N11
U1_N12: TP228.1, U1.N12
U1_N13: TP229.1, U1.N13
U1_N14: TP230.1, U1.N14
U1_N15: TP231.1, U1.N15
U1_N16: TP232.1, U1.N16
U1_N17: TP233.1, U1.N17
U1_N18: TP234.1, U1.N18
U1_P1: TP235.1, U1.P1
U1_P2: TP236.1, U1.P2
U1_P3: TP237.1, U1.P3
U1_P4: TP238.1, U1.P4
U1_P5: TP239.1, U1.P5
U1_P6: TP240.1, U1.P6
U1_P7: TP241.1, U1.P7
U1_P8: TP242.1, U1.P8
U1_P9: TP243.1, U1.P9
U1_P10: TP244.1, U1.P10
U1_P11: TP245.1, U1.P11
U1_P12: TP246.1, U1.P12
U1_P13: TP247.1, U1.P13
U1_P14: TP248.1, U1.P14
U1_P15: TP249.1, U1.P15
U1_P16: TP250.1, U1.P16
U1_P17: TP251.1, U1.P17
U1_P18: TP252.1, U1.P18
U1_R1: TP253.1, U1.R1
U1_R2: TP254.1, U1.R2
U1_R3: TP255.1, U1.R3
U1_R4: TP256.1, U1.R4
U1_R5: TP257.1, U1.R5
U1_R6: TP258.1, U1.R6
U1_R7: TP259.1, U1.R7
U1_R8: TP260.1, U1.R8
U1_R9: TP261.1, U1.R9
U1_R10: TP262.1, U1.R10
U1_R11: TP263.1, U1.R11
U1_R12: TP264.1, U1.R12
U1_R13: TP265.1, U1.R13
U1_R14: TP266.1, U1.R14
U1_R15: TP267.1, U1.R15
U1_R16: TP268.1, U1.R16
U1_R17: TP269.1, U1.R17
U1_R18: TP270.1, U1.R18
U1_T1: TP271.1, U1.T1
U1_T2: TP272.1, U1.T2
U1_T3: TP273.1, U1.T3
U1_T4: TP274.1, U1.T4
U1_T5: TP275.1, U1.T5
U1_T6: TP276.1, U1.T6
U1_T7: TP277.1, U1.T7
U1_T8: TP278.1, U1.T8
U1_T9: TP279.1, U1.T9
U1_T10: TP280.1, U1.T10
U1_T11: TP281.1, U1.T11
U1_T12: TP282.1, U1.T12
U1_T13: TP283.1, U1.T13
U1_T14: TP284.1, U1.T14
U1_T15: TP285.1, U1.T15
U1_T16: TP286.1, U1.T16
U1_T17: TP287.1, U1.T17
U1_T18: TP288.1, U1.T18
U1_U1: TP289.1, U1.U1
U1_U2: TP290.1, U1.U2
U1_U3: TP291.1, U1.U3
U1_U4: TP292.1, U1.U4
U1_U5: TP293.1, U1.U5
U1_U6: TP294.1, U1.U6
U1_U7: TP295.1, U1.U7
U1_U8: TP296.1, U1.U8
U1_U9: TP297.1, U1.U9
U1_U10: TP298.1, U1.U10
U1_U11: TP299.1, U1.U11
U1_U12: TP300.1, U1.U12
U1_U13: TP301.1, U1.U13
U1_U14: TP302.1, U1.U14
U1_U15: TP303.1, U1.U15
U1_U16: TP304.1, U1.U16
U1_U17: TP305.1, U1.U17
U1_U18: TP306.1, U1.U18
U1_V1: TP307.1, U1.V1
U1_V2: TP308.1, U1.V2
U1_V3: TP309.1, U1.V3
U1_V4: TP310.1, U1.V4
U1_V5: TP311.1, U1.V5
U1_V6: TP312.1, U1.V6
U1_V7: TP313.1, U1.V7
U1_V8: TP314.1, U1.V8
U1_V9: TP315.1, U1.V9
U1_V10: TP316.1, U1.V10
U1_V11: TP317.1, U1.V11
U1_V12: TP318.1, U1.V12
U1_V13: TP319.1, U1.V13
U1_V14: TP320.1, U1.V14
U1_V15: TP321.1, U1.V15
U1_V16: TP322.1, U1.V16
U1_V17: TP323.1, U1.V17
U1_V18: TP324.1, U1.V18
